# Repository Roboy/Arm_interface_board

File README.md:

# Arm_interface_board
Board containing all the control units and power distribution for the servos in the arms.

## Hardware Setup
1. Check and/or solder the clock crystal on the board. Bridge the appropiate pads in order to enable it or make use
  of the extra two pins.
2. Crimp the connectors for power/i2c and the servos according to the following diagram:
   - **Power/I2C:**\
      5V |||||| GND         ]\
      SDA|||||| blah        ] TODO
   - **Servos:**\
      The connectors on the board are designed to receive a connection that starting with the indexing pin on the left
      (to the right) look like this:
      - 5V
      - GND
      - SIGNAL\

   Be careful and rearrange the connections before crimping if needed. Also make sure the cables exit the connector in an
   appropiate direction, to avoid loops.

## Software and flashing guide
The board can be programmed with the Arduino IDE but some setup is required.
### For boards with the ATMEGA328PB
This is partially the result of a mistake in ordering the uControllers,
so the board is not actually designed to fit the chip. Even so it works without
much modifications, although one should exercise special care to **tristate** the pins
that are connected directly to power (A & B).
#### Prerequisites
- MCUdude's [MiniCore](https://github.com/MCUdude/MiniCore) (and all it's dependencies:)
- Arduino IDE v.1.6.4 or greater
#### Setup
You need to install extra packages to enable compatibility with this chip in
the Arduino IDE.\
Add the following URLs to the **Additional Boards Manager URLs**:
```
https://mcudude.github.io/MiniCore/package_MCUdude_MiniCore_index.json
```
This one enables and advanced bootloader and the extra functions in the PB series.
For this you also need the latest AVR toolchain (version 1.6.206). Add:
```
https://downloads.arduino.cc/packages/package_avr_3.6.0_index.json
```
to your Boards Manager.\

After you do this you can install the Minicore and update the Arduino AVR boards to
1.6.207 (AVR toolchain).
#### Flashing
To flash the board you need to use an ISP programmer. The easiest way is to use
an arduino as the programmer. You can do this by flashing any Arduino board with
the code from *Examples*>*11. ArduinoISP*>*ArduinoISP*. Afterwards you can select
the AVR chip from the Minicore boards and configure it for the specified clock, etc.
With all options set you can burn the bootloader by selecting "Arduino as ISP"
in the Programmer window.\

Sadly with this version of the AVR toolchain, for some reason the flashing does not work out of the box.
You require the latest version of **avrdude**, and the only way is by compiling
it from the [source](https://github.com/sigmike/avrdude).\
After you install it the flashing procedure is a bit different. You have to first
compile your code, and then using your freshly built avrdude version upload it
to your board.

UPDATE: downgrade to avr boards 1.6.23 and install arduino isp on atmega 2560. switch to 1.6.207 and install bootloader.

sudo ./avrdude -Cavrdude.conf -v -pm328p -cstk500v1 -P/dev/ttyACM0 -b19200 -D -Uflash:w:/tmp/arduino_build_XXXXXX/roboy_arm_board.ino.hex:i -F

in above command replace XXXXXX with your build number

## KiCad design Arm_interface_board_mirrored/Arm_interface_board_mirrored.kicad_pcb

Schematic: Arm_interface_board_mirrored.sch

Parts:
Aref1: TEST_1P; TestPoint_Pad_D1.0mm
C1, C3, C8, C9, C10, C11, C17: 100n; C_0402_1005Metric
C2: 22u; CP_Elec_4x5.3
C4, C5: 22p; C_0402_1005Metric
C6, C7: 1u; C_0402_1005Metric
D1: LED; LED_0603_1608Metric
D2: USER_LED(PB0); LED_0603_1608Metric
J1: CONN_02X08; PinHeader_2x08_P1.27mm_Vertical
J3: ICSP; PinHeader_2x03_P2.54mm_Vertical
J6: JST_PHD_connector_02x05_angled_male; JST_S10B-PHDSS_2x05x2.00mm_Angled
JP1: XTAL_EN1; SolderJumper-3_P1.3mm_Open_RoundedPad1.0x1.5mm
JP2: XTAL_EN2; SolderJumper-3_P1.3mm_Open_RoundedPad1.0x1.5mm
MK1, MK2, MK3: Mounting_Hole_PAD; MountingHole_2.2mm_M2_DIN965_Pad
R1: 1mOhm; R_1206_3216Metric
R2, R9: 10k; R_0402_1005Metric
R8: 1k; R_0402_1005Metric
S-IN1: TEST_1P; TestPoint_Pad_D1.0mm
SW1: SW_Push; SW_SPST_SKQG
SW2: USER_SW; SW_SPST_KXT3
U1: INA180; SOT-23-5
U2: BMI160; Bosch_LGA-14_3x2.5mm_P0.5mm
U3: NTS0102; X2SON-8_1.4x1mm_P0.35mm
U4: ATMEGA328PB-AU; TQFP-32_7x7mm_P0.8mm
U5: MIC5504-3.3YM5; SOT-23-5
Y1: TSX-3225 20MHz; Crystal_SMD_TXC_7M-4Pin_3.2x2.5mm

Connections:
+3V3: C7.1, C9.1, C10.1, J1.1, U2.5, U2.8, U2.12, U3.3, U3.6, U5.5
+5V: C1.1, C2.1, C3.1, C6.1, C17.1, J1.2, J3.2, R1.1, R2.1, R8.2, U1.4, U1.5, U3.7, U4.4 (VCC), U4.18 (AVCC), U5.1, U5.3; also elsewhere on the board
+5VP: J6.4, J6.6, J6.8, J6.10, R1.2, U1.3
/MISO: J1.7, J3.1, U4.16 ((MISO0/RXD1/PTCXY)PB4)
/MOSI: J1.5, J3.4, U4.15 ((MOSI0/TXD1/OC2A/PTCXY)PB3)
/PB0: R9.2, U4.12 ((CLKO/ICP1/PTCXY)PB0)
/PB6: J1.11, JP1.1
/PB7: J1.13, JP2.3
/PD0: J1.10, U4.30 ((RXD0/OC3A/PTCXY)PD0)
/PD1: J1.3, U4.31 ((TXD0/OC4A/PTCXY)PD1)
/PD2: J1.4, U4.32 ((OC3B/OC4B/INT0/PTCXY)PD2)
/PD4: SW2.1, U4.2 ((XCK0/T0/PTCXY)PD4)
/PD7: J1.12, U4.11 ((AIN1/PTCXY)PD7)
/RESET: C11.1, J3.5, R2.2, SW1.1, U4.29 ((~RESET~)PC6)
/SCK: J1.9, J3.3, U4.17 ((XCK0/SCK0/PTCXY)PB5)
/SCL: J1.16, J6.2, U4.28 ((SCL0/ADC5/PTCY)PC5)
/SCL1_H: U3.1, U4.6 (PE1(PTCXY/SCL1/T4))
/SCL1_L: J1.8, U2.13, U3.4
/SDA: J1.14, J6.1, U4.27 ((SDA0/ADC4/PTCY)PC4)
/SDA1_H: U3.8, U4.3 (PE0(PTCXY/SDA1/ICP4/ACO))
/SDA1_L: J1.6, U2.14, U3.5
/Servos/Current_adc1: U4.23 ((MISO1/ADC0/PTCY)PC0); also elsewhere on the board
/Servos/Current_adc2: U4.24 ((SCK1/ADC1/PTCY)PC1); also elsewhere on the board
/Servos/Current_adc3: U4.25 ((ADC2/PTCY)PC2); also elsewhere on the board
/Servos/Current_adc4: U4.26 ((ADC3/PTCY)PC3); also elsewhere on the board
/Servos/Current_adc5: U4.19 (PE2(PTCY/ADC6/ICP3/~SS1~)); also elsewhere on the board
/Servos/Servo_pwm1: U4.13 ((OC1A/PTCXY)PB1); also elsewhere on the board
/Servos/Servo_pwm2: U4.14 ((OC1B/~SS0~/PTCXY)PB2); also elsewhere on the board
/Servos/Servo_pwm3: U4.1 ((OC2B/INT1/PTCXY)PD3); also elsewhere on the board
/Servos/Servo_pwm4: U4.9 ((OC0B/T1/PTCXY)PD5); also elsewhere on the board
/Servos/Servo_pwm5: U4.10 ((OC0A/AIN0/PTCXY)PD6); also elsewhere on the board
GND: C1.2, C2.2, C3.2, C4.1, C5.1, C6.2, C7.2, C8.2, C9.2, C10.2, C11.2, C17.2, D1.1, D2.1, J1.15, J3.6, J6.3, J6.5, J6.7, J6.9, MK1.1, MK2.1, MK3.1, SW1.2, SW2.2, U1.2, U2.1, U2.6, U2.7, U3.2, U4.5 (GND), U4.21 (GND), U5.2, Y1.2, Y1.4; also elsewhere on the board
unnamed: Aref1.1, C8.1, U4.20 (AREF)
unnamed: C4.2, JP1.3, Y1.1
unnamed: C5.2, JP2.1, Y1.3
unnamed: D1.2, R8.1
unnamed: D2.2, R9.1
unnamed: JP1.2, U4.7 ((XTAL1/TOSC1)PB6)
unnamed: JP2.2, U4.8 ((XTAL2/TOSC2)PB7)
unnamed: S-IN1.1, U1.1, U4.22 (PE3(PTCY/ADC7/T3/MOSI1))

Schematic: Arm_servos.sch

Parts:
C12, C13, C14, C15, C16: 100n; C_0402_1005Metric
J16, J17, J18, J19, J20: CONN_01X04; TE-Connectivity_Micro-Match_connector_02x02_Pitch_1.27mm
R3, R4, R5, R6, R7: 10mOhm; R_1206_3216Metric
S1, S2, S3, S4, S5: TEST_1P; TestPoint_Pad_D1.0mm
U7, U8, U9, U10, U11: INA180; SOT-23-5

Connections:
+5V: C12.1, C13.1, C14.1, C15.1, C16.1, R3.2, R4.2, R5.2, R6.2, R7.2, U7.3, U7.5, U8.3, U8.5, U9.3, U9.5, U10.3, U10.5, U11.3, U11.5; also elsewhere on the board
/Servos/Current_adc1: S1.1, U7.1; also elsewhere on the board
/Servos/Current_adc2: S2.1, U8.1; also elsewhere on the board
/Servos/Current_adc3: S3.1, U9.1; also elsewhere on the board
/Servos/Current_adc4: S4.1, U10.1; also elsewhere on the board
/Servos/Current_adc5: S5.1, U11.1; also elsewhere on the board
/Servos/Servo_pwm1: J16.3; also elsewhere on the board
/Servos/Servo_pwm2: J17.3; also elsewhere on the board
/Servos/Servo_pwm3: J18.3; also elsewhere on the board
/Servos/Servo_pwm4: J19.3; also elsewhere on the board
/Servos/Servo_pwm5: J20.3; also elsewhere on the board
GND: C12.2, C13.2, C14.2, C15.2, C16.2, J16.2, J16.4, J17.2, J17.4, J18.2, J18.4, J19.2, J19.4, J20.2, J20.4, U7.2, U8.2, U9.2, U10.2, U11.2; also elsewhere on the board
unnamed: J16.1, R3.1, U7.4
unnamed: J17.1, R4.1, U8.4
unnamed: J18.1, R5.1, U9.4
unnamed: J19.1, R6.1, U10.4
unnamed: J20.1, R7.1, U11.4

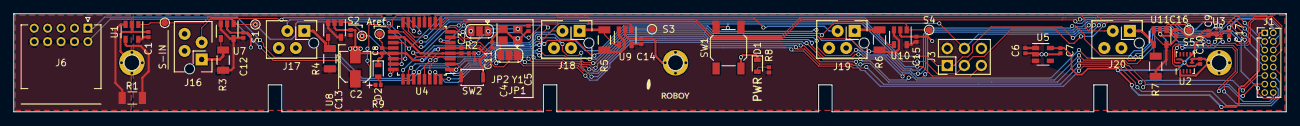
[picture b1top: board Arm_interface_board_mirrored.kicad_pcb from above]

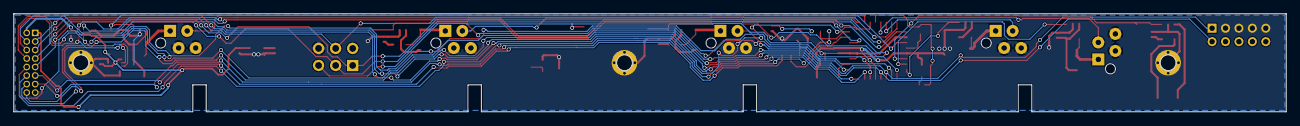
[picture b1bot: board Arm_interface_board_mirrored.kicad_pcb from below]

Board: 2 copper layers, 189.6 x 14.6 mm, 61 parts (3 on the bottom side), 45 nets.

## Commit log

2017-07-06 Initial commit, added dxf drawings and started to create the connector footprints
2017-07-20 Random work on custom footprints
2018-01-15 Cleaned up board outline. Changed main uController to the Atmega328 in a 32 pin package.
2018-01-19 Partially finished the schematic and readied footprints. Basic uController infrastructure, and current sensing mechanism with shunts and amps.
2018-01-23 Switched to KiCad 5 and made some great progress. Also some minor corrections.
2018-01-31 After battling against track widths and mechanical aspects, routing is complete\!
2018-01-31 Forgot to add files. God since when has this been happening\?
2018-02-03 Added Roboy logo and cleaned silkscreen
2018-03-20 Create README.md
    Vital infos ;)
2018-03-20 Readme edit
2018-03-20 Moar readme!
2018-04-01 with communication fpga i2c and imu readout using bitbang
2018-04-01 with correct imu readout hand
2018-04-03 with arduino config
2018-04-03 removed
2018-04-03 with soft i2c version
2018-04-08 Finished the fixes that make the board fully compatible with the PB variant of the Atmega328 chip. Also added an user LED and button. Started mirroring the board manually for the other arm
2018-04-08 Some more work on the mirrored board
2018-04-10 Finished! The mirrored board is finished!
2018-04-10 Cleaned up a bit and started the panel
2018-04-10 Finished the panel, boards now ready to be ordered.
2018-04-10 Cleaned up old panel files and zipped the new ones.
2018-04-10 Felt too fancy and exported the gerbers with extended atributes enabled. Of course the people @ PCBWAY couldn't open them -.- .
2018-06-15 Updated BOM.
2018-10-09 update flash procedure
